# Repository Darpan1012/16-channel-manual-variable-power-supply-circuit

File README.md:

16 channel 0-15 V dual supply power source circuit

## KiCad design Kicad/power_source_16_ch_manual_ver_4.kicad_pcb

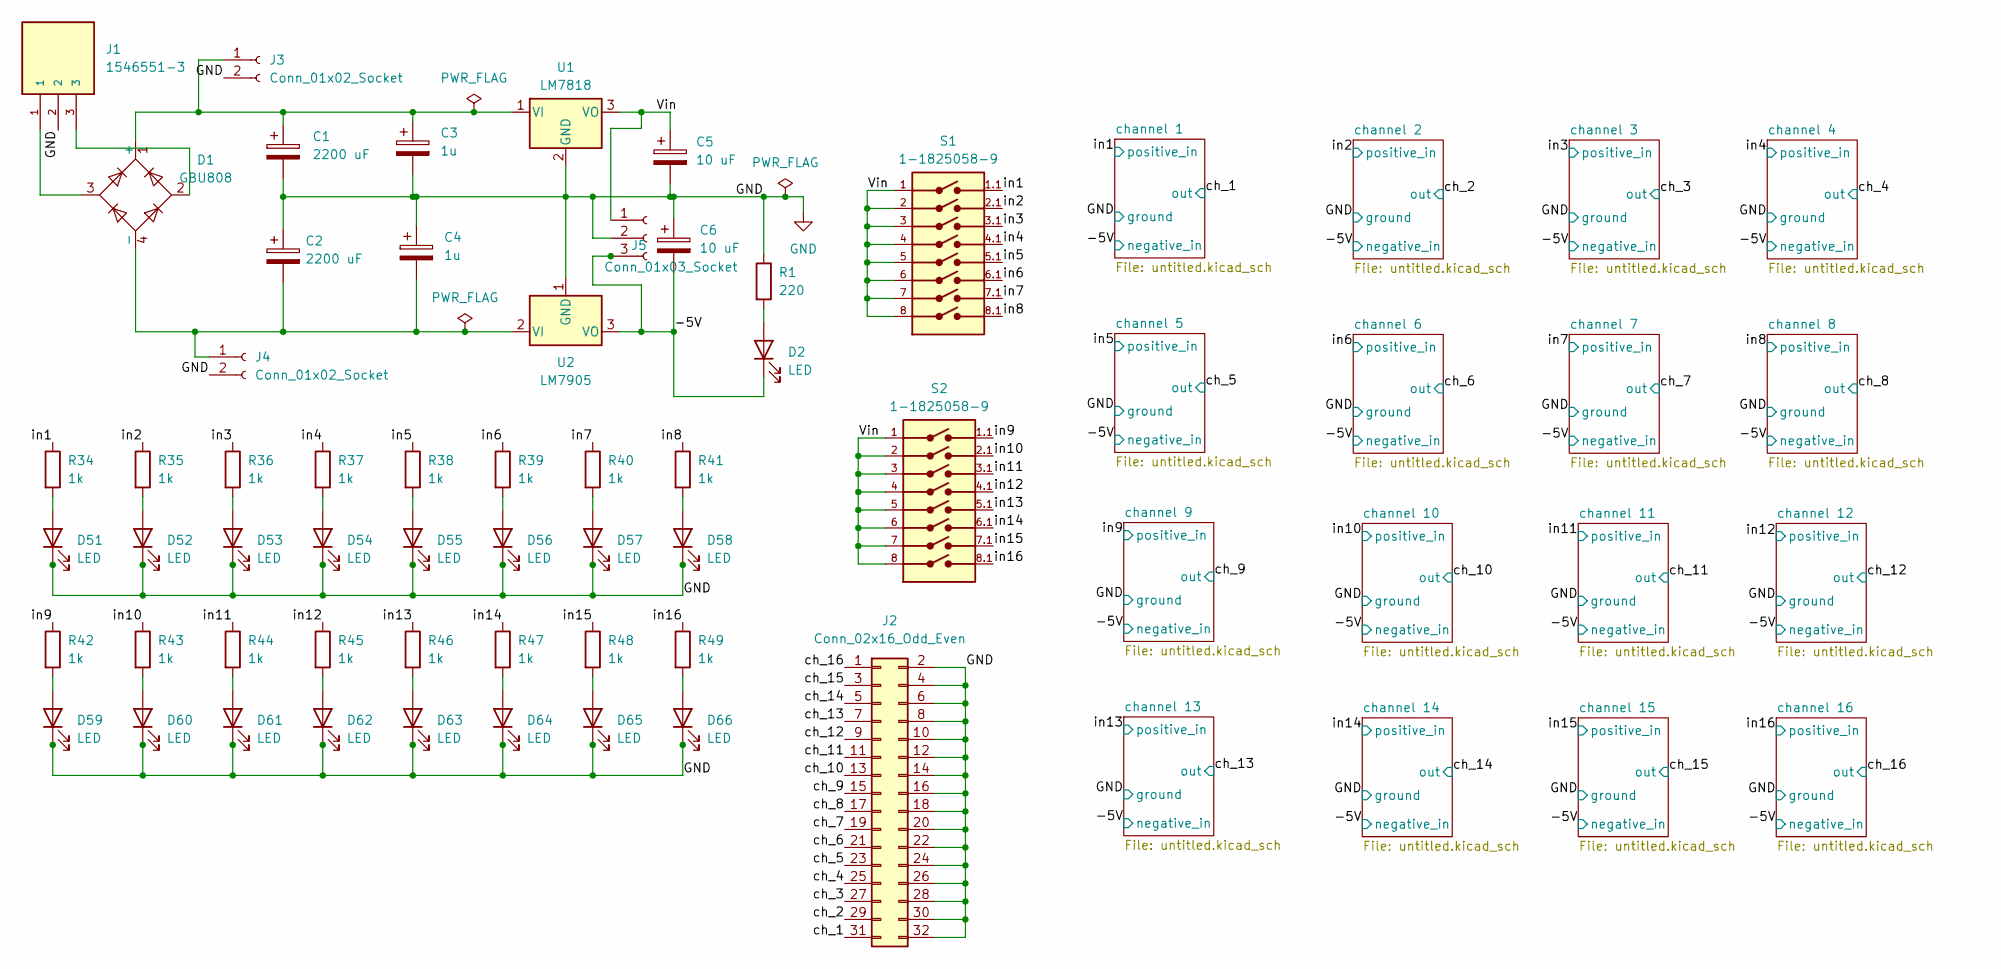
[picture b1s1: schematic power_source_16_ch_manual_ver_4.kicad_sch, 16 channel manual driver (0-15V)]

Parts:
C1, C2: 2200 uF; CP_Elec_18x17.5; Part Number VE-222M1VTR-1816; LCSC PN C249505
C3, C4: 1u; CP_Elec_4x5.4; Part Number RVT1H1R0M0405; LCSC PN C3348
C5, C6: 10 uF; CP_Elec_4x5.4; Part Number RVT1E100M0405; LCSC PN C3343
D1: GBU808; Diode_Bridge_Vishay_GBU; Part Number GBU808; LCSC PN C3072
D2, D51, D52, D53, D54, D55, D56, D57, D58, D59, D60, D61, D62, D63, D64, D65, D66: LED; LED_0603_1608Metric; Part Number KT-0603R; LCSC PN C2286
J1: 1546551-3; TE_1546551-3; PARTREV R
J2: Conn_02x16_Odd_Even; PinHeader_2x16_P2.54mm_Vertical; Part Number DS1023-2*16SF11; LCSC PN C132130
J3, J4: Conn_01x02_Socket; PinHeader_1x02_P2.54mm_Vertical; Part Number DS1023-1x2SF11; LCSC PN C7509512
J5: Conn_01x03_Socket; PinHeader_1x03_P2.54mm_Vertical; Part Number DS1023-1x3SF11; LCSC PN C7509516
R1: 220; R_0805_2012Metric; Part Number 0805W8F2200T5E; LCSC PN C17557
R34, R35, R36, R37, R38, R39, R40, R41, R42, R43, R44, R45, R46, R47, R48, R49: 1k; R_0805_2012Metric; Part Number 0805W8F1001T5E; LCSC PN C17513
S1, S2: 1-1825058-9; SW_1-1825058-9; PARTREV S4; LCSC PN C266184
U1: LM7818; TO-220-3_Vertical; Part Number L7818CV-DG; LCSC PN C15411
U2: LM7905; TO-220-3_Vertical; Part Number L7905CV-DG; LCSC PN C3799

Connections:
/-5V: C6.2, D2.1 (K), J5.3, U2.3 (VO); also elsewhere on the board
/Vin: C5.1, J5.1, S1.1, S1.2, S1.3, S1.4, S1.5, S1.6, S1.7, S1.8, S2.1, S2.2, S2.3, S2.4, S2.5, S2.6, S2.7, S2.8, U1.3 (VO)
/ch_1: J2.31; also elsewhere on the board
/ch_2: J2.29; also elsewhere on the board
/ch_3: J2.27; also elsewhere on the board
/ch_4: J2.25; also elsewhere on the board
/ch_5: J2.23; also elsewhere on the board
/ch_6: J2.21; also elsewhere on the board
/ch_7: J2.19; also elsewhere on the board
/ch_8: J2.17; also elsewhere on the board
/ch_9: J2.15; also elsewhere on the board
/ch_10: J2.13; also elsewhere on the board
/ch_11: J2.11; also elsewhere on the board
/ch_12: J2.9; also elsewhere on the board
/ch_13: J2.7; also elsewhere on the board
/ch_14: J2.5; also elsewhere on the board
/ch_15: J2.3; also elsewhere on the board
/ch_16: J2.1; also elsewhere on the board
/in1: R34.1, S1.1.1; also elsewhere on the board
/in2: R35.1, S1.2.1; also elsewhere on the board
/in3: R36.1, S1.3.1; also elsewhere on the board
/in4: R37.1, S1.4.1; also elsewhere on the board
/in5: R38.1, S1.5.1; also elsewhere on the board
/in6: R39.1, S1.6.1; also elsewhere on the board
/in7: R40.1, S1.7.1; also elsewhere on the board
/in8: R41.1, S1.8.1; also elsewhere on the board
/in9: R42.1, S2.1.1; also elsewhere on the board
/in10: R43.1, S2.2.1; also elsewhere on the board
/in11: R44.1, S2.3.1; also elsewhere on the board
/in12: R45.1, S2.4.1; also elsewhere on the board
/in13: R46.1, S2.5.1; also elsewhere on the board
/in14: R47.1, S2.6.1; also elsewhere on the board
/in15: R48.1, S2.7.1; also elsewhere on the board
/in16: R49.1, S2.8.1; also elsewhere on the board
GND: C1.2, C2.1, C3.2, C4.1, C5.2, C6.1, D51.1 (K), D52.1 (K), D53.1 (K), D54.1 (K), D55.1 (K), D56.1 (K), D57.1 (K), D58.1 (K), D59.1 (K), D60.1 (K), D61.1 (K), D62.1 (K), D63.1 (K), D64.1 (K), D65.1 (K), D66.1 (K), J1.2, J2.2, J2.4, J2.6, J2.8, J2.10, J2.12, J2.14, J2.16, J2.18, J2.20, J2.22, J2.24, J2.26, J2.28, J2.30, J2.32, J3.2, J4.2, J5.2, R1.1, U1.2 (GND), U2.1 (GND); also elsewhere on the board
unnamed: C1.1, C3.1, D1.1 (+), J3.1, U1.1 (VI)
unnamed: C2.2, C4.2, D1.4 (-), J4.1, U2.2 (VI)
unnamed: D1.2, J1.3
unnamed: D1.3, J1.1
unnamed: D2.2 (A), R1.2
unnamed: D51.2 (A), R34.2
unnamed: D52.2 (A), R35.2
unnamed: D53.2 (A), R36.2
unnamed: D54.2 (A), R37.2
unnamed: D55.2 (A), R38.2
unnamed: D56.2 (A), R39.2
unnamed: D57.2 (A), R40.2
unnamed: D58.2 (A), R41.2
unnamed: D59.2 (A), R42.2
unnamed: D60.2 (A), R43.2
unnamed: D61.2 (A), R44.2
unnamed: D62.2 (A), R45.2
unnamed: D63.2 (A), R46.2
unnamed: D64.2 (A), R47.2
unnamed: D65.2 (A), R48.2
unnamed: D66.2 (A), R49.2

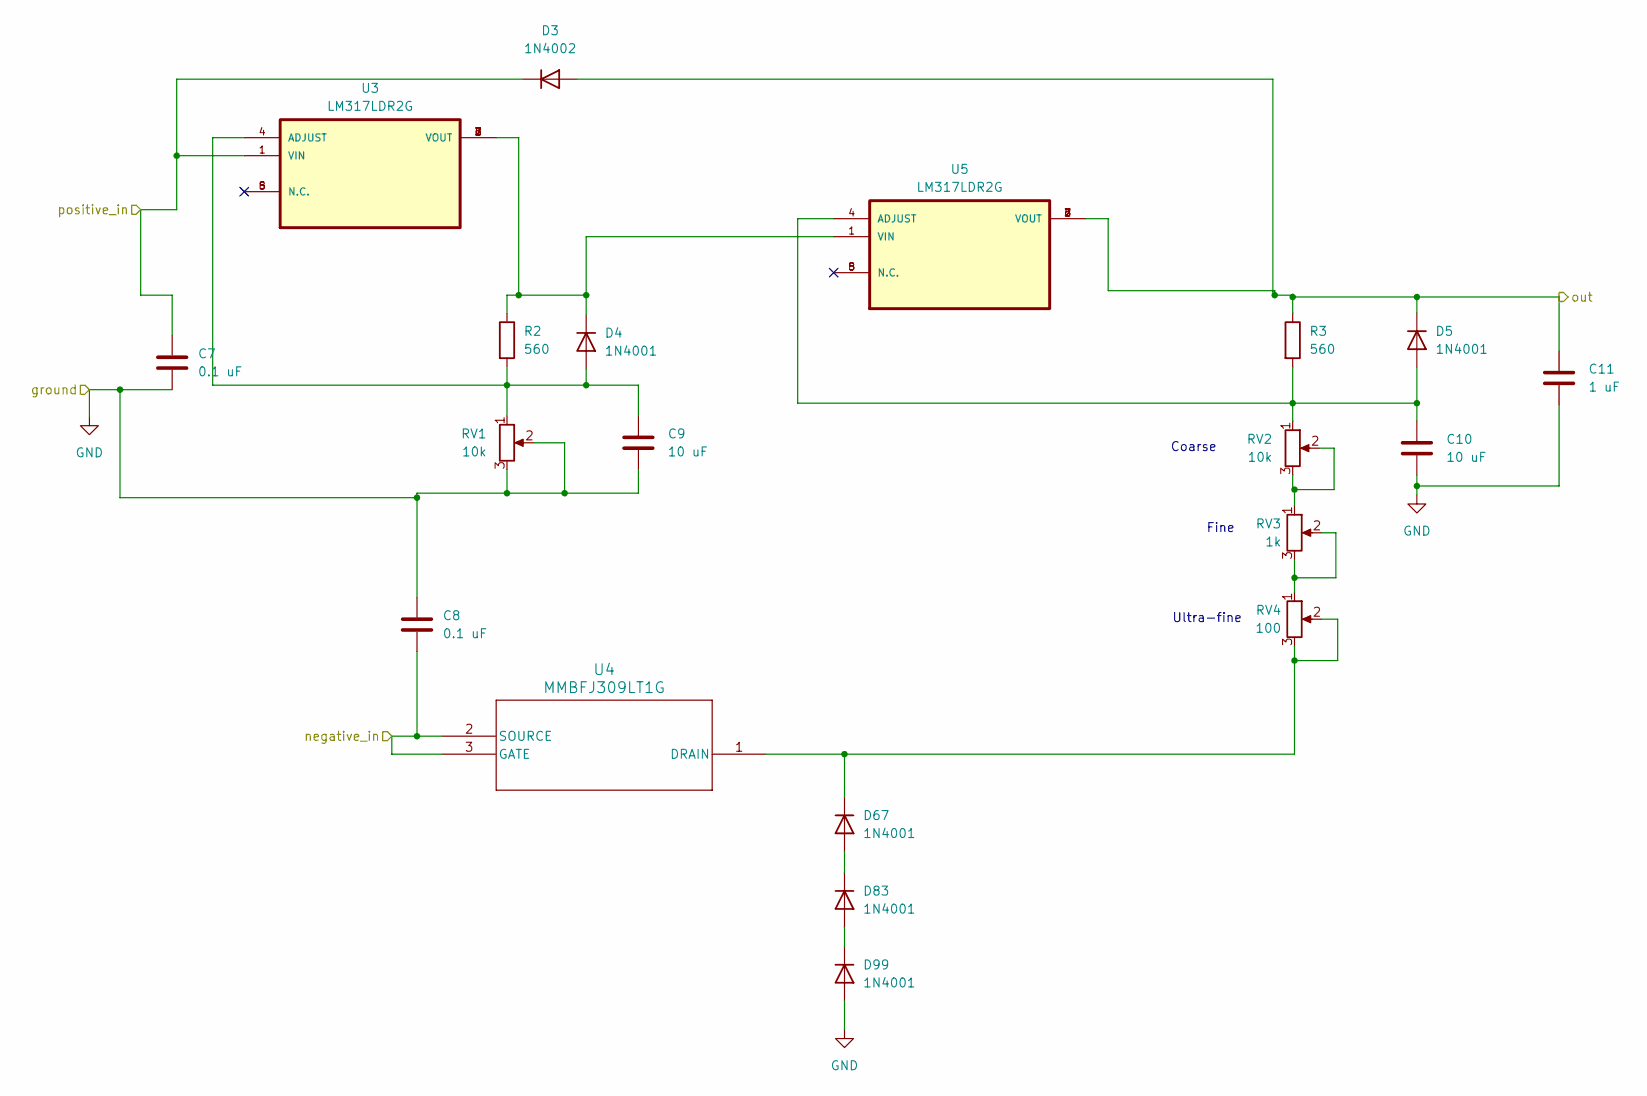
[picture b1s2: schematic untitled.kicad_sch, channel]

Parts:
C7, C8: 0.1 uF; C_0603_1608Metric; Part Number CC0603KRX7R9BB104; LCSC PN C14663
C9, C10: 10 uF; C_1206_3216Metric; Part Number CL31A106KBHNNNE; LCSC PN C13585
C11: 1 uF; C_1206_3216Metric; Part Number CL31B105KBHNNNE; LCSC PN C1848
D3: 1N4002; D_SOD-123F; Part Number 1N4002W; LCSC PN C169542
D4, D5, D67, D83, D99: 1N4001; D_SOD-123F; Part Number 1N4001W; LCSC PN C162732
R2, R3: 560; R_0805_2012Metric; Part Number 0805W8F5600T5E; LCSC PN C28636
RV1, RV2: 10k; Potentiometer_Runtron_RM-065_Vertical; Part Number WH06-2C-103(10K); LCSC PN C5205043
RV3: 1k; Potentiometer_Runtron_RM-065_Vertical; Part Number WH06-2C-102(1K); LCSC PN C5205040
RV4: 100; TRIM_3362P-1-103; Part Number 3362P-1-101; LCSC PN C118959
U3, U5: LM317LDR2G; SOIC127P600X175-8N; Part Number LM317LD13TR; LCSC PN C81457
U4: MMBFJ309LT1G; SOT-23_ONS-L; Part Number MMBFJ309LT1G; LCSC PN C58012

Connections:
/-5V: C8.2, U4.2 (SOURCE), U4.3 (GATE); also elsewhere on the board
/ch_1: C11.1, D3.2 (A), D5.1 (K), R3.1, U5.2 (VOUT), U5.3 (VOUT), U5.6 (VOUT), U5.7 (VOUT); also elsewhere on the board
/in1: C7.1, D3.1 (K), U3.1 (VIN); also elsewhere on the board
GND: C7.2, C8.1, C9.2, C10.2, C11.2, D99.2 (A), RV1.2, RV1.3; also elsewhere on the board
unnamed: C9.1, D4.2 (A), R2.2, RV1.1, U3.4 (ADJUST)
unnamed: D4.1 (K), R2.1, U3.2 (VOUT), U3.3 (VOUT), U3.6 (VOUT), U3.7 (VOUT), U5.1 (VIN)
unnamed: C10.1, D5.2 (A), R3.2, RV2.1, U5.4 (ADJUST)
unnamed: D67.2 (A), D83.1 (K)
unnamed: D67.1 (K), RV4.2, RV4.3, U4.1 (DRAIN)
unnamed: D83.2 (A), D99.1 (K)
unnamed: RV2.2, RV2.3, RV3.1
unnamed: RV3.2, RV3.3, RV4.1

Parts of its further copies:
C12, C13, C17, C18, C22, C23, C27, C28, C32, C33, C37, C38, C42, C43, C47, C48, C52, C53, C57, C58, C62, C63, C67, C68, C72, C73, C77, C78, C82, C83: 0.1 uF; C_0603_1608Metric; Part Number CC0603KRX7R9BB104; LCSC PN C14663
C14, C15, C19, C20, C24, C25, C29, C30, C34, C35, C39, C40, C44, C45, C49, C50, C54, C55, C59, C60, C64, C65, C69, C70, C74, C75, C79, C80, C84, C85: 10 uF; C_1206_3216Metric; Part Number CL31A106KBHNNNE; LCSC PN C13585
C16, C21, C26, C31, C36, C41, C46, C51, C56, C61, C66, C71, C76, C81, C86: 1 uF; C_1206_3216Metric; Part Number CL31B105KBHNNNE; LCSC PN C1848
D6, D9, D12, D15, D18, D21, D24, D27, D30, D33, D36, D39, D42, D45, D48: 1N4002; D_SOD-123F; Part Number 1N4002W; LCSC PN C169542
D7, D8, D10, D11, D13, D14, D16, D17, D19, D20, D22, D23, D25, D26, D28, D29, D31, D32, D34, D35, D37, D38, D40, D41, D43, D44, D46, D47, D49, D50, D68, D69, D70, D71, D72, D73, D74, D75, D76, D77, D78, D79, D80, D81, D82, D84, D85, D86, D87, D88, D89, D90, D91, D92, D93, D94, D95, D96, D97, D98, D100, D101, D102, D103, D104, D105, D106, D107, D108, D109, D110, D111, D112, D113, D114: 1N4001; D_SOD-123F; Part Number 1N4001W; LCSC PN C162732
R4, R5, R6, R7, R8, R9, R10, R11, R12, R13, R14, R15, R16, R17, R18, R19, R20, R21, R22, R23, R24, R25, R26, R27, R28, R29, R30, R31, R32, R33: 560; R_0805_2012Metric; Part Number 0805W8F5600T5E; LCSC PN C28636
RV5, RV6, RV9, RV10, RV13, RV14, RV17, RV18, RV21, RV22, RV25, RV26, RV29, RV30, RV33, RV34, RV37, RV38, RV41, RV42, RV45, RV46, RV49, RV50, RV53, RV54, RV57, RV58, RV61, RV62: 10k; Potentiometer_Runtron_RM-065_Vertical; Part Number WH06-2C-103(10K); LCSC PN C5205043
RV7, RV11, RV15, RV19, RV23, RV27, RV31, RV35, RV39, RV43, RV47, RV51, RV55, RV59, RV63: 1k; Potentiometer_Runtron_RM-065_Vertical; Part Number WH06-2C-102(1K); LCSC PN C5205040
RV8, RV12, RV16, RV20, RV24, RV28, RV32, RV36, RV40, RV44, RV48, RV52, RV56, RV60, RV64: 100; TRIM_3362P-1-103; Part Number 3362P-1-101; LCSC PN C118959
U6, U8, U9, U11, U12, U14, U15, U17, U18, U20, U21, U23, U24, U26, U27, U29, U30, U32, U33, U35, U36, U38, U39, U41, U42, U44, U45, U47, U48, U50: LM317LDR2G; SOIC127P600X175-8N; Part Number LM317LD13TR; LCSC PN C81457
U7, U10, U13, U16, U19, U22, U25, U28, U31, U34, U37, U40, U43, U46, U49: MMBFJ309LT1G; SOT-23_ONS-L; Part Number MMBFJ309LT1G; LCSC PN C58012

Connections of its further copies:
/-5V: C13.2, C18.2, C23.2, C28.2, C33.2, C38.2, C43.2, C48.2, C53.2, C58.2, C63.2, C68.2, C73.2, C78.2, C83.2, U7.2 (SOURCE), U7.3 (GATE), U10.2 (SOURCE), U10.3 (GATE), U13.2 (SOURCE), U13.3 (GATE), U16.2 (SOURCE), U16.3 (GATE), U19.2 (SOURCE), U19.3 (GATE), U22.2 (SOURCE), U22.3 (GATE), U25.2 (SOURCE), U25.3 (GATE), U28.2 (SOURCE), U28.3 (GATE), U31.2 (SOURCE), U31.3 (GATE), U34.2 (SOURCE), U34.3 (GATE), U37.2 (SOURCE), U37.3 (GATE), U40.2 (SOURCE), U40.3 (GATE), U43.2 (SOURCE), U43.3 (GATE), U46.2 (SOURCE), U46.3 (GATE), U49.2 (SOURCE), U49.3 (GATE); also elsewhere on the board
/ch_2: C16.1, D6.2 (A), D8.1 (K), R5.1, U8.2 (VOUT), U8.3 (VOUT), U8.6 (VOUT), U8.7 (VOUT); also elsewhere on the board
/ch_3: C21.1, D9.2 (A), D11.1 (K), R7.1, U11.2 (VOUT), U11.3 (VOUT), U11.6 (VOUT), U11.7 (VOUT); also elsewhere on the board
/ch_4: C26.1, D12.2 (A), D14.1 (K), R9.1, U14.2 (VOUT), U14.3 (VOUT), U14.6 (VOUT), U14.7 (VOUT); also elsewhere on the board
/ch_5: C31.1, D15.2 (A), D17.1 (K), R11.1, U17.2 (VOUT), U17.3 (VOUT), U17.6 (VOUT), U17.7 (VOUT); also elsewhere on the board
/ch_6: C36.1, D18.2 (A), D20.1 (K), R13.1, U20.2 (VOUT), U20.3 (VOUT), U20.6 (VOUT), U20.7 (VOUT); also elsewhere on the board
/ch_7: C41.1, D21.2 (A), D23.1 (K), R15.1, U23.2 (VOUT), U23.3 (VOUT), U23.6 (VOUT), U23.7 (VOUT); also elsewhere on the board
/ch_8: C46.1, D24.2 (A), D26.1 (K), R17.1, U26.2 (VOUT), U26.3 (VOUT), U26.6 (VOUT), U26.7 (VOUT); also elsewhere on the board
/ch_9: C51.1, D27.2 (A), D29.1 (K), R19.1, U29.2 (VOUT), U29.3 (VOUT), U29.6 (VOUT), U29.7 (VOUT); also elsewhere on the board
/ch_10: C56.1, D30.2 (A), D32.1 (K), R21.1, U32.2 (VOUT), U32.3 (VOUT), U32.6 (VOUT), U32.7 (VOUT); also elsewhere on the board
/ch_11: C61.1, D33.2 (A), D35.1 (K), R23.1, U35.2 (VOUT), U35.3 (VOUT), U35.6 (VOUT), U35.7 (VOUT); also elsewhere on the board
/ch_12: C66.1, D36.2 (A), D38.1 (K), R25.1, U38.2 (VOUT), U38.3 (VOUT), U38.6 (VOUT), U38.7 (VOUT); also elsewhere on the board
/ch_13: C71.1, D39.2 (A), D41.1 (K), R27.1, U41.2 (VOUT), U41.3 (VOUT), U41.6 (VOUT), U41.7 (VOUT); also elsewhere on the board
/ch_14: C76.1, D42.2 (A), D44.1 (K), R29.1, U44.2 (VOUT), U44.3 (VOUT), U44.6 (VOUT), U44.7 (VOUT); also elsewhere on the board
/ch_15: C81.1, D45.2 (A), D47.1 (K), R31.1, U47.2 (VOUT), U47.3 (VOUT), U47.6 (VOUT), U47.7 (VOUT); also elsewhere on the board
/ch_16: C86.1, D48.2 (A), D50.1 (K), R33.1, U50.2 (VOUT), U50.3 (VOUT), U50.6 (VOUT), U50.7 (VOUT); also elsewhere on the board
/in2: C12.1, D6.1 (K), U6.1 (VIN); also elsewhere on the board
/in3: C17.1, D9.1 (K), U9.1 (VIN); also elsewhere on the board
/in4: C22.1, D12.1 (K), U12.1 (VIN); also elsewhere on the board
/in5: C27.1, D15.1 (K), U15.1 (VIN); also elsewhere on the board
/in6: C32.1, D18.1 (K), U18.1 (VIN); also elsewhere on the board
/in7: C37.1, D21.1 (K), U21.1 (VIN); also elsewhere on the board
/in8: C42.1, D24.1 (K), U24.1 (VIN); also elsewhere on the board
/in9: C47.1, D27.1 (K), U27.1 (VIN); also elsewhere on the board
/in10: C52.1, D30.1 (K), U30.1 (VIN); also elsewhere on the board
/in11: C57.1, D33.1 (K), U33.1 (VIN); also elsewhere on the board
/in12: C62.1, D36.1 (K), U36.1 (VIN); also elsewhere on the board
/in13: C67.1, D39.1 (K), U39.1 (VIN); also elsewhere on the board
/in14: C72.1, D42.1 (K), U42.1 (VIN); also elsewhere on the board
/in15: C77.1, D45.1 (K), U45.1 (VIN); also elsewhere on the board
/in16: C82.1, D48.1 (K), U48.1 (VIN); also elsewhere on the board
GND: C12.2, C13.1, C14.2, C15.2, C16.2, C17.2, C18.1, C19.2, C20.2, C21.2, C22.2, C23.1, C24.2, C25.2, C26.2, C27.2, C28.1, C29.2, C30.2, C31.2, C32.2, C33.1, C34.2, C35.2, C36.2, C37.2, C38.1, C39.2, C40.2, C41.2, C42.2, C43.1, C44.2, C45.2, C46.2, C47.2, C48.1, C49.2, C50.2, C51.2, C52.2, C53.1, C54.2, C55.2, C56.2, C57.2, C58.1, C59.2, C60.2, C61.2, C62.2, C63.1, C64.2, C65.2, C66.2, C67.2, C68.1, C69.2, C70.2, C71.2, C72.2, C73.1, C74.2, C75.2, C76.2, C77.2, C78.1, C79.2, C80.2, C81.2, C82.2, C83.1, C84.2, C85.2, C86.2, D100.2 (A), D101.2 (A), D102.2 (A), D103.2 (A), D104.2 (A), D105.2 (A), D106.2 (A), D107.2 (A), D108.2 (A), D109.2 (A), D110.2 (A), D111.2 (A), D112.2 (A), D113.2 (A), D114.2 (A), RV5.2, RV5.3, RV9.2, RV9.3, RV13.2, RV13.3, RV17.2, RV17.3, RV21.2, RV21.3, RV25.2, RV25.3, RV29.2, RV29.3, RV33.2, RV33.3, RV37.2, RV37.3, RV41.2, RV41.3, RV45.2, RV45.3, RV49.2, RV49.3, RV53.2, RV53.3, RV57.2, RV57.3, RV61.2, RV61.3; also elsewhere on the board
unnamed: C14.1, D7.2 (A), R4.2, RV5.1, U6.4 (ADJUST)
unnamed: D7.1 (K), R4.1, U6.2 (VOUT), U6.3 (VOUT), U6.6 (VOUT), U6.7 (VOUT), U8.1 (VIN)
unnamed: C15.1, D8.2 (A), R5.2, RV6.1, U8.4 (ADJUST)
unnamed: C19.1, D10.2 (A), R6.2, RV9.1, U9.4 (ADJUST)
unnamed: D10.1 (K), R6.1, U9.2 (VOUT), U9.3 (VOUT), U9.6 (VOUT), U9.7 (VOUT), U11.1 (VIN)
unnamed: C20.1, D11.2 (A), R7.2, RV10.1, U11.4 (ADJUST)
unnamed: C24.1, D13.2 (A), R8.2, RV13.1, U12.4 (ADJUST)
unnamed: D13.1 (K), R8.1, U12.2 (VOUT), U12.3 (VOUT), U12.6 (VOUT), U12.7 (VOUT), U14.1 (VIN)
unnamed: C25.1, D14.2 (A), R9.2, RV14.1, U14.4 (ADJUST)
unnamed: C29.1, D16.2 (A), R10.2, RV17.1, U15.4 (ADJUST)
unnamed: D16.1 (K), R10.1, U15.2 (VOUT), U15.3 (VOUT), U15.6 (VOUT), U15.7 (VOUT), U17.1 (VIN)
unnamed: C30.1, D17.2 (A), R11.2, RV18.1, U17.4 (ADJUST)
unnamed: C34.1, D19.2 (A), R12.2, RV21.1, U18.4 (ADJUST)
unnamed: D19.1 (K), R12.1, U18.2 (VOUT), U18.3 (VOUT), U18.6 (VOUT), U18.7 (VOUT), U20.1 (VIN)
unnamed: C35.1, D20.2 (A), R13.2, RV22.1, U20.4 (ADJUST)
unnamed: C39.1, D22.2 (A), R14.2, RV25.1, U21.4 (ADJUST)
unnamed: D22.1 (K), R14.1, U21.2 (VOUT), U21.3 (VOUT), U21.6 (VOUT), U21.7 (VOUT), U23.1 (VIN)
unnamed: C40.1, D23.2 (A), R15.2, RV26.1, U23.4 (ADJUST)
unnamed: C44.1, D25.2 (A), R16.2, RV29.1, U24.4 (ADJUST)
unnamed: D25.1 (K), R16.1, U24.2 (VOUT), U24.3 (VOUT), U24.6 (VOUT), U24.7 (VOUT), U26.1 (VIN)
unnamed: C45.1, D26.2 (A), R17.2, RV30.1, U26.4 (ADJUST)
unnamed: C49.1, D28.2 (A), R18.2, RV33.1, U27.4 (ADJUST)
unnamed: D28.1 (K), R18.1, U27.2 (VOUT), U27.3 (VOUT), U27.6 (VOUT), U27.7 (VOUT), U29.1 (VIN)
unnamed: C50.1, D29.2 (A), R19.2, RV34.1, U29.4 (ADJUST)
unnamed: C54.1, D31.2 (A), R20.2, RV37.1, U30.4 (ADJUST)
unnamed: D31.1 (K), R20.1, U30.2 (VOUT), U30.3 (VOUT), U30.6 (VOUT), U30.7 (VOUT), U32.1 (VIN)
unnamed: C55.1, D32.2 (A), R21.2, RV38.1, U32.4 (ADJUST)
unnamed: C59.1, D34.2 (A), R22.2, RV41.1, U33.4 (ADJUST)
unnamed: D34.1 (K), R22.1, U33.2 (VOUT), U33.3 (VOUT), U33.6 (VOUT), U33.7 (VOUT), U35.1 (VIN)
unnamed: C60.1, D35.2 (A), R23.2, RV42.1, U35.4 (ADJUST)
unnamed: C64.1, D37.2 (A), R24.2, RV45.1, U36.4 (ADJUST)
unnamed: D37.1 (K), R24.1, U36.2 (VOUT), U36.3 (VOUT), U36.6 (VOUT), U36.7 (VOUT), U38.1 (VIN)
unnamed: C65.1, D38.2 (A), R25.2, RV46.1, U38.4 (ADJUST)
unnamed: C69.1, D40.2 (A), R26.2, RV49.1, U39.4 (ADJUST)
unnamed: D40.1 (K), R26.1, U39.2 (VOUT), U39.3 (VOUT), U39.6 (VOUT), U39.7 (VOUT), U41.1 (VIN)
unnamed: C70.1, D41.2 (A), R27.2, RV50.1, U41.4 (ADJUST)
unnamed: C74.1, D43.2 (A), R28.2, RV53.1, U42.4 (ADJUST)
unnamed: D43.1 (K), R28.1, U42.2 (VOUT), U42.3 (VOUT), U42.6 (VOUT), U42.7 (VOUT), U44.1 (VIN)
unnamed: C75.1, D44.2 (A), R29.2, RV54.1, U44.4 (ADJUST)
unnamed: C79.1, D46.2 (A), R30.2, RV57.1, U45.4 (ADJUST)
unnamed: D46.1 (K), R30.1, U45.2 (VOUT), U45.3 (VOUT), U45.6 (VOUT), U45.7 (VOUT), U47.1 (VIN)
unnamed: C80.1, D47.2 (A), R31.2, RV58.1, U47.4 (ADJUST)
unnamed: C84.1, D49.2 (A), R32.2, RV61.1, U48.4 (ADJUST)
unnamed: D49.1 (K), R32.1, U48.2 (VOUT), U48.3 (VOUT), U48.6 (VOUT), U48.7 (VOUT), U50.1 (VIN)
unnamed: C85.1, D50.2 (A), R33.2, RV62.1, U50.4 (ADJUST)
unnamed: D68.2 (A), D84.1 (K)
unnamed: D68.1 (K), RV8.2, RV8.3, U7.1 (DRAIN)
unnamed: D69.2 (A), D85.1 (K)
unnamed: D69.1 (K), RV12.2, RV12.3, U10.1 (DRAIN)
unnamed: D70.2 (A), D86.1 (K)
unnamed: D70.1 (K), RV16.2, RV16.3, U13.1 (DRAIN)
unnamed: D71.2 (A), D87.1 (K)
unnamed: D71.1 (K), RV20.2, RV20.3, U16.1 (DRAIN)
unnamed: D72.2 (A), D88.1 (K)
unnamed: D72.1 (K), RV24.2, RV24.3, U19.1 (DRAIN)
unnamed: D73.2 (A), D89.1 (K)
unnamed: D73.1 (K), RV28.2, RV28.3, U22.1 (DRAIN)
unnamed: D74.2 (A), D90.1 (K)
unnamed: D74.1 (K), RV32.2, RV32.3, U25.1 (DRAIN)
unnamed: D75.2 (A), D91.1 (K)
unnamed: D75.1 (K), RV36.2, RV36.3, U28.1 (DRAIN)
unnamed: D76.2 (A), D92.1 (K)
unnamed: D76.1 (K), RV40.2, RV40.3, U31.1 (DRAIN)
unnamed: D77.2 (A), D93.1 (K)
unnamed: D77.1 (K), RV44.2, RV44.3, U34.1 (DRAIN)
unnamed: D78.2 (A), D94.1 (K)
unnamed: D78.1 (K), RV48.2, RV48.3, U37.1 (DRAIN)
unnamed: D79.2 (A), D95.1 (K)
unnamed: D79.1 (K), RV52.2, RV52.3, U40.1 (DRAIN)
unnamed: D80.2 (A), D96.1 (K)
unnamed: D80.1 (K), RV56.2, RV56.3, U43.1 (DRAIN)
unnamed: D81.2 (A), D97.1 (K)
unnamed: D81.1 (K), RV60.2, RV60.3, U46.1 (DRAIN)
unnamed: D82.2 (A), D98.1 (K)
unnamed: D82.1 (K), RV64.2, RV64.3, U49.1 (DRAIN)
unnamed: D84.2 (A), D100.1 (K)
unnamed: D85.2 (A), D101.1 (K)
unnamed: D86.2 (A), D102.1 (K)
unnamed: D87.2 (A), D103.1 (K)
unnamed: D88.2 (A), D104.1 (K)
unnamed: D89.2 (A), D105.1 (K)
unnamed: D90.2 (A), D106.1 (K)
unnamed: D91.2 (A), D107.1 (K)
unnamed: D92.2 (A), D108.1 (K)
unnamed: D93.2 (A), D109.1 (K)
unnamed: D94.2 (A), D110.1 (K)
unnamed: D95.2 (A), D111.1 (K)
unnamed: D96.2 (A), D112.1 (K)
unnamed: D97.2 (A), D113.1 (K)
unnamed: D98.2 (A), D114.1 (K)
unnamed: RV6.2, RV6.3, RV7.1
unnamed: RV7.2, RV7.3, RV8.1
unnamed: RV10.2, RV10.3, RV11.1
unnamed: RV11.2, RV11.3, RV12.1
unnamed: RV14.2, RV14.3, RV15.1
unnamed: RV15.2, RV15.3, RV16.1
unnamed: RV18.2, RV18.3, RV19.1
unnamed: RV19.2, RV19.3, RV20.1
unnamed: RV22.2, RV22.3, RV23.1
unnamed: RV23.2, RV23.3, RV24.1
unnamed: RV26.2, RV26.3, RV27.1
unnamed: RV27.2, RV27.3, RV28.1
unnamed: RV30.2, RV30.3, RV31.1
unnamed: RV31.2, RV31.3, RV32.1
unnamed: RV34.2, RV34.3, RV35.1
unnamed: RV35.2, RV35.3, RV36.1
unnamed: RV38.2, RV38.3, RV39.1
unnamed: RV39.2, RV39.3, RV40.1
unnamed: RV42.2, RV42.3, RV43.1
unnamed: RV43.2, RV43.3, RV44.1
unnamed: RV46.2, RV46.3, RV47.1
unnamed: RV47.2, RV47.3, RV48.1
unnamed: RV50.2, RV50.3, RV51.1
unnamed: RV51.2, RV51.3, RV52.1
unnamed: RV54.2, RV54.3, RV55.1
unnamed: RV55.2, RV55.3, RV56.1
unnamed: RV58.2, RV58.3, RV59.1
unnamed: RV59.2, RV59.3, RV60.1
unnamed: RV62.2, RV62.3, RV63.1
unnamed: RV63.2, RV63.3, RV64.1

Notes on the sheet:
Ultra-fine
Fine
Coarse

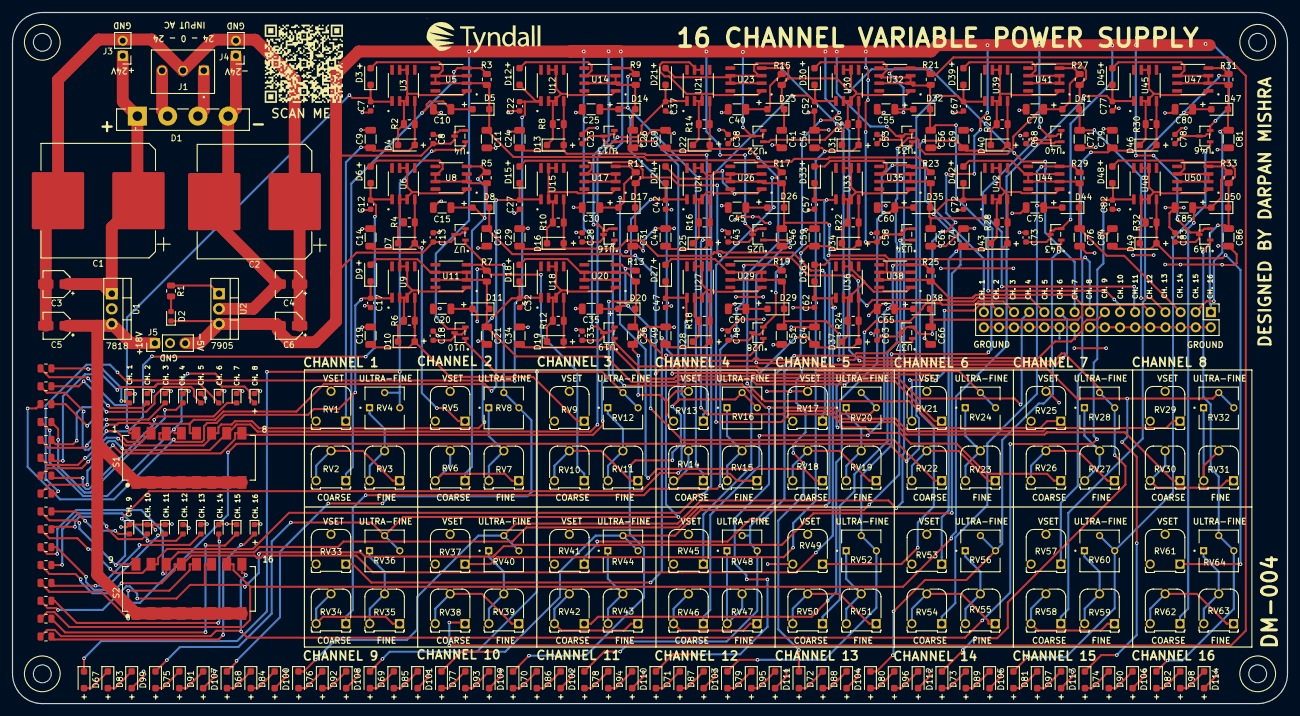
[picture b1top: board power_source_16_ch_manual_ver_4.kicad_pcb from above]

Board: 2 copper layers, 214.0 x 116.0 mm, 370 parts (0 on the bottom side), 184 nets.

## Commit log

2025-11-14 Create Circuit
2025-11-14 Create pcb
2025-11-14 Create gerber
2025-11-14 Create ltspice
2025-11-14 Create screenshots
2025-11-14 Create manual pdf
